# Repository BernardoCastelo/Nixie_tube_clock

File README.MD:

# Cold cathode display clock

## Components:
> - IN12 displays
> - Firebeetle ESP-32
> - NTE74141 BCD−to−Decimal Decoder
> - 74HC4094N 8-bit Shift Register

- https://photos.app.goo.gl/ndDG4vCSE8pfqmn36

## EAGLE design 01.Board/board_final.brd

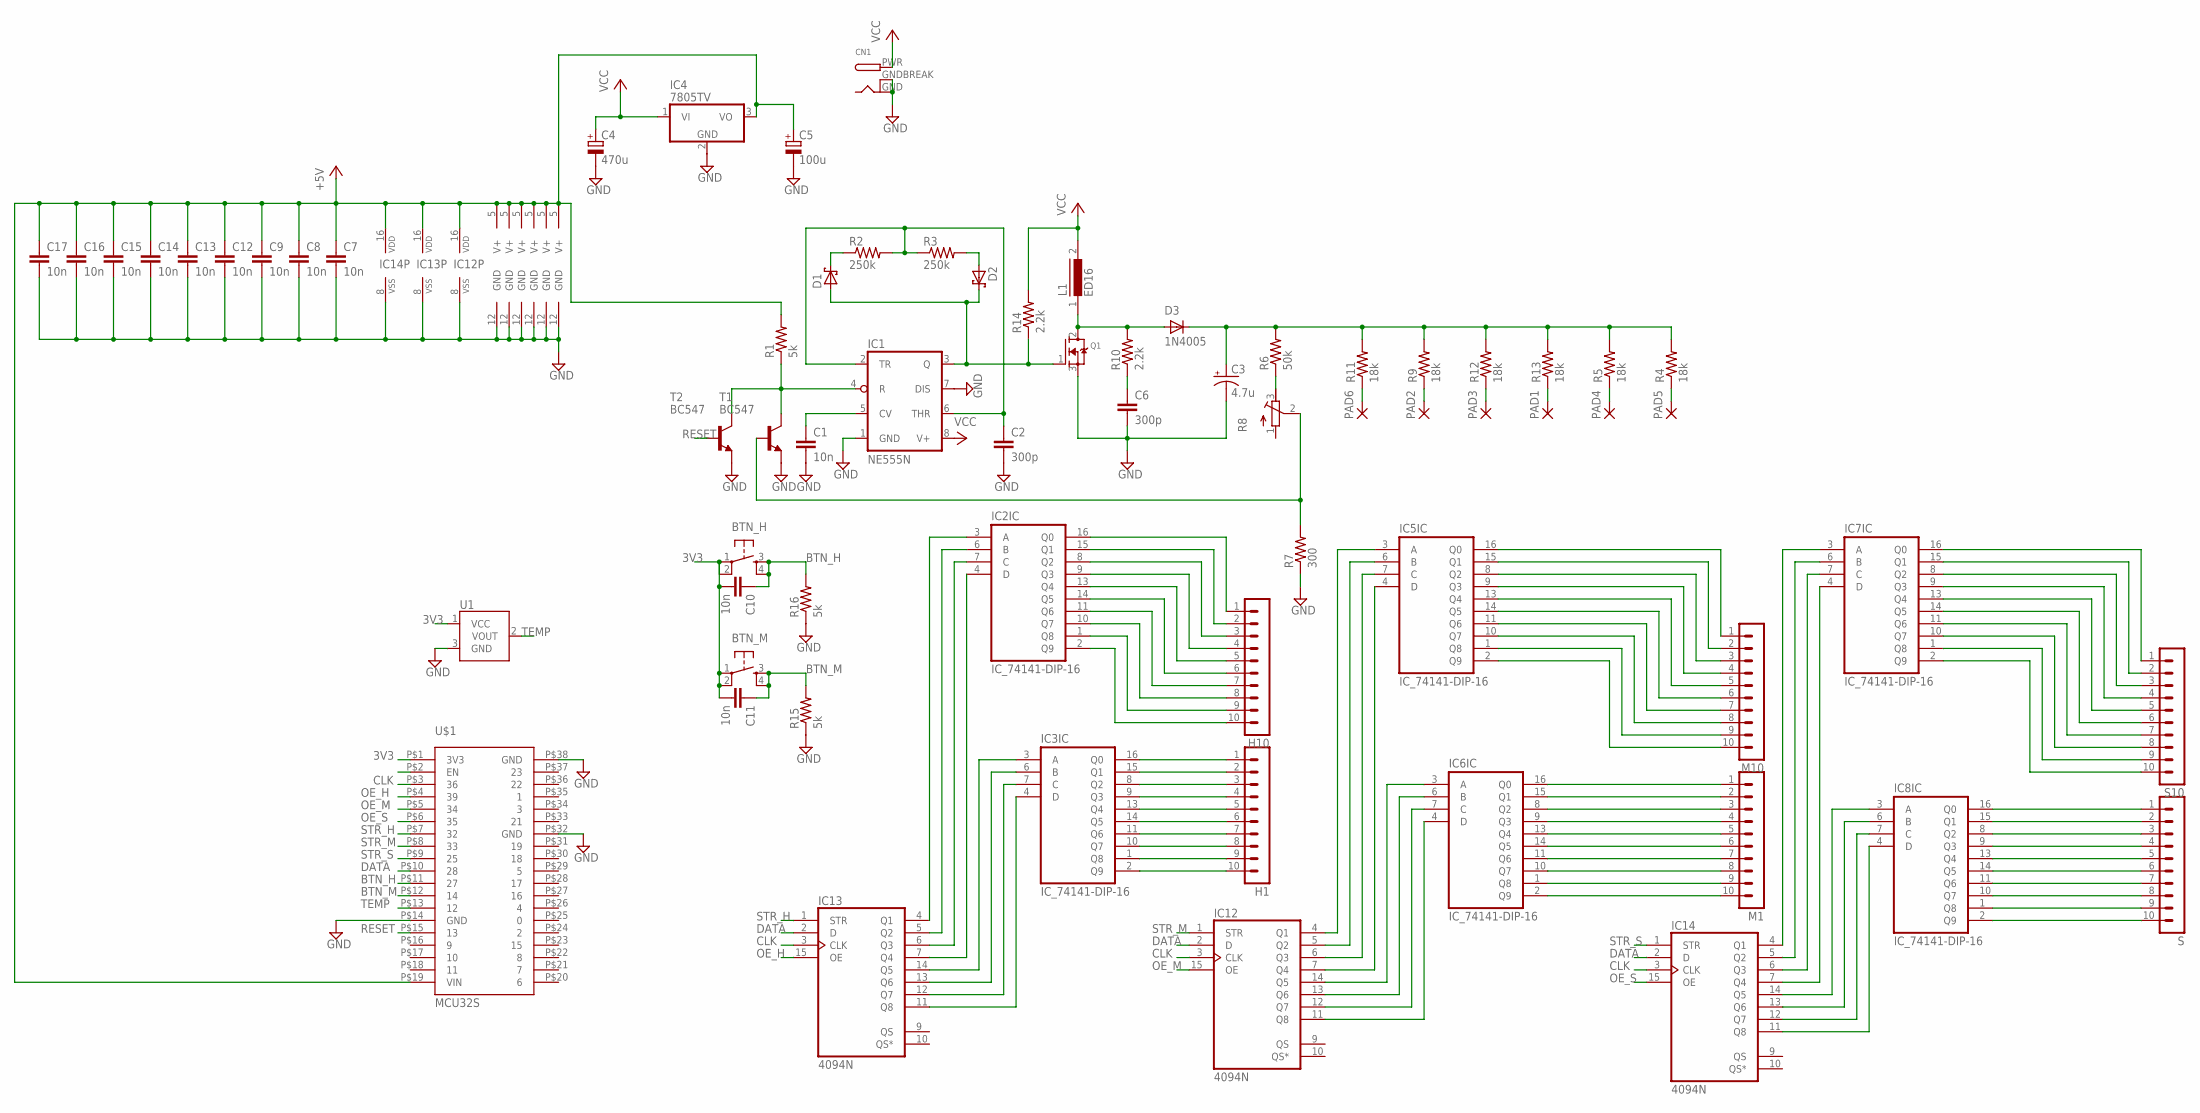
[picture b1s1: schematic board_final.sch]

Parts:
BTN_H: TAC_SWITCHPTH; TACTILE-PTH
BTN_M: TAC_SWITCHPTH; TACTILE-PTH
C1, C7, C8, C9, C10, C11, C12, C13, C14, C15, C16, C17: 10n; C050-030X075
C2, C6: 300p; C050-030X075
C3: 4.7u; E3,5-10
C4: 470u; E5-8,5
C5: 100u; E5-8,5
CN1: DCBARRELPTH; DCJACK_2MM_PTH
D1, D2: SCHOTTKY-DIODEF126Z12; F126Z12
D3: 1N4005; DO41-10
H1, H10: MA10-1
IC1: NE555N; DIL08
IC2, IC3, IC5, IC6, IC7, IC8: IC_74141-DIP-16; DIL16
IC4: 7805TV; TO220V
IC12, IC13, IC14: 4094N; DIL16
L1: ED16
M1, M10: MA10-1
PAD1, PAD2, PAD3, PAD4, PAD5, PAD6: 3,17/1,3
Q1: MOSFET-NGDS_TO220V; TO220V
R1, R15, R16: 5k; 0207/10
R2, R3: 250k; 0207/10
R4, R5, R9, R11, R12, R13: 18k; 0207/10
R6: 50k; 0207/10
R7: 300; 0207/10
R8: R-TRIMM3296W; RTRIM3296W
R10, R14: 2.2k; 0207/10
S, S10: MA10-1
T1, T2: BC547; TO92
U1: TMP36GT9; TO-92
U$1: MCU32S; NODEMCU32S

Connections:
3V3: BTN_H.1, BTN_H.2, BTN_M.1, BTN_M.2, C10.2, C11.2, U1.1 (VCC), U$1.P$1 (3V3)
BTN_H: BTN_H.3, BTN_H.4, C10.1, R16.2, U$1.P$11 (27)
BTN_M: BTN_M.3, BTN_M.4, C11.1, R15.2, U$1.P$12 (14)
CLK: IC12.3 (CLK), IC13.3 (CLK), IC14.3 (CLK), U$1.P$3 (36)
DATA: IC12.2 (D), IC13.2 (D), IC14.2 (D), U$1.P$10 (28)
GND: C1.2, C2.2, C3.-, C4.-, C5.-, C6.2, C7.2, C8.2, C9.2, C12.2, C13.2, C14.2, C15.2, C16.2, C17.2, CN1.GND, CN1.GNDBREAK, IC1.1 (GND), IC1.7 (DIS), IC2.12 (GND), IC3.12 (GND), IC4.2 (GND), IC5.12 (GND), IC6.12 (GND), IC7.12 (GND), IC8.12 (GND), IC12.8 (VSS), IC13.8 (VSS), IC14.8 (VSS), Q1.3 (S), R7.1, R15.1, R16.1, T1.1 (E), T2.1 (E), U1.3 (GND), U$1.P$14 (GND), U$1.P$32 (GND), U$1.P$38 (GND)
unnamed: C1.1, IC1.5 (CV)
unnamed: C2.1, IC1.2 (TR), IC1.6 (THR), R2.2, R3.1
unnamed: C3.+, D3.C, R4.2, R5.2, R6.2, R9.2, R11.2, R12.2, R13.2
unnamed: D1.A, D2.C, IC1.3 (Q), Q1.1 (G), R14.1
unnamed: IC1.4 (R), R1.1, T1.3 (C), T2.3 (C)
unnamed: H10.1, IC2.16 (Q0)
unnamed: D2.A, R3.2
unnamed: D1.C, R2.1
unnamed: IC2.3 (A), IC13.4 (Q1)
unnamed: D3.A, L1.1, Q1.2 (D), R10.2
unnamed: H10.2, IC2.15 (Q1)
unnamed: H10.3, IC2.8 (Q2)
unnamed: H10.4, IC2.9 (Q3)
unnamed: H10.5, IC2.13 (Q4)
unnamed: H10.6, IC2.14 (Q5)
unnamed: H10.7, IC2.11 (Q6)
unnamed: H10.8, IC2.10 (Q7)
unnamed: H10.9, IC2.1 (Q8)
unnamed: H10.10, IC2.2 (Q9)
unnamed: PAD6.1, R11.1
unnamed: IC2.7 (C), IC13.6 (Q3)
unnamed: IC2.6 (B), IC13.5 (Q2)
unnamed: IC2.4 (D), IC13.7 (Q4)
unnamed: H1.1, IC3.16 (Q0)
unnamed: H1.2, IC3.15 (Q1)
unnamed: H1.3, IC3.8 (Q2)
unnamed: C6.1, R10.1
unnamed: H1.4, IC3.9 (Q3)
unnamed: H1.5, IC3.13 (Q4)
unnamed: H1.6, IC3.14 (Q5)
unnamed: H1.7, IC3.11 (Q6)
unnamed: R6.1, R8.3 (E)
unnamed: R7.2, R8.2 (S), T1.2 (B)
unnamed: H1.8, IC3.10 (Q7)
unnamed: H1.9, IC3.1 (Q8)
unnamed: H1.10, IC3.2 (Q9)
unnamed: IC3.7 (C), IC13.12 (Q7)
unnamed: IC3.6 (B), IC13.13 (Q6)
unnamed: IC3.4 (D), IC13.11 (Q8)
unnamed: PAD2.1, R9.1
unnamed: IC3.3 (A), IC13.14 (Q5)
unnamed: IC6.2 (Q9), M1.10
unnamed: IC6.1 (Q8), M1.9
unnamed: IC6.10 (Q7), M1.8
unnamed: IC6.11 (Q6), M1.7
unnamed: IC6.14 (Q5), M1.6
unnamed: IC6.13 (Q4), M1.5
unnamed: IC6.9 (Q3), M1.4
unnamed: IC6.8 (Q2), M1.3
unnamed: IC6.15 (Q1), M1.2
unnamed: IC6.16 (Q0), M1.1
unnamed: IC5.7 (C), IC12.6 (Q3)
unnamed: IC5.6 (B), IC12.5 (Q2)
unnamed: IC5.4 (D), IC12.7 (Q4)
unnamed: PAD3.1, R12.1
unnamed: IC5.3 (A), IC12.4 (Q1)
unnamed: IC5.16 (Q0), M10.1
unnamed: IC5.15 (Q1), M10.2
unnamed: IC5.8 (Q2), M10.3
unnamed: IC5.9 (Q3), M10.4
unnamed: IC5.13 (Q4), M10.5
unnamed: IC5.14 (Q5), M10.6
unnamed: IC5.11 (Q6), M10.7
unnamed: IC5.10 (Q7), M10.8
unnamed: IC5.1 (Q8), M10.9
unnamed: IC5.2 (Q9), M10.10
unnamed: IC6.6 (B), IC12.13 (Q6)
unnamed: IC8.16 (Q0), S.1
unnamed: IC8.15 (Q1), S.2
unnamed: PAD1.1, R13.1
unnamed: IC6.3 (A), IC12.14 (Q5)
unnamed: IC7.3 (A), IC14.4 (Q1)
unnamed: IC8.8 (Q2), S.3
unnamed: IC8.9 (Q3), S.4
unnamed: IC8.13 (Q4), S.5
unnamed: IC8.14 (Q5), S.6
unnamed: IC8.11 (Q6), S.7
unnamed: IC8.10 (Q7), S.8
unnamed: IC8.2 (Q9), S.10
unnamed: IC8.1 (Q8), S.9
unnamed: IC7.16 (Q0), S10.1
unnamed: IC7.6 (B), IC14.5 (Q2)
unnamed: IC7.7 (C), IC14.6 (Q3)
unnamed: IC7.4 (D), IC14.7 (Q4)
unnamed: PAD4.1, R5.1
unnamed: IC8.3 (A), IC14.14 (Q5)
unnamed: IC8.6 (B), IC14.13 (Q6)
unnamed: IC7.15 (Q1), S10.2
unnamed: IC7.8 (Q2), S10.3
unnamed: IC7.9 (Q3), S10.4
unnamed: IC7.13 (Q4), S10.5
unnamed: IC7.14 (Q5), S10.6
unnamed: IC7.11 (Q6), S10.7
unnamed: IC7.10 (Q7), S10.8
unnamed: IC7.1 (Q8), S10.9
unnamed: IC7.2 (Q9), S10.10
unnamed: IC8.7 (C), IC14.12 (Q7)
unnamed: IC8.4 (D), IC14.11 (Q8)
unnamed: PAD5.1, R4.1
unnamed: IC6.7 (C), IC12.12 (Q7)
unnamed: IC6.4 (D), IC12.11 (Q8)
OE_H: IC13.15 (OE), U$1.P$4 (39)
OE_M: IC12.15 (OE), U$1.P$5 (34)
OE_S: IC14.15 (OE), U$1.P$6 (35)
RESET: T2.2 (B), U$1.P$15 (13)
STR_H: IC13.1 (STR), U$1.P$7 (32)
STR_M: IC12.1 (STR), U$1.P$8 (33)
STR_S: IC14.1 (STR), U$1.P$9 (25)
TEMP: U1.2 (VOUT), U$1.P$13 (12)
V+: C5.+, C7.1, C8.1, C9.1, C12.1, C13.1, C14.1, C15.1, C16.1, C17.1, IC2.5 (V+), IC3.5 (V+), IC4.3 (VO), IC5.5 (V+), IC6.5 (V+), IC7.5 (V+), IC8.5 (V+), IC12.16 (VDD), IC13.16 (VDD), IC14.16 (VDD), R1.2, U$1.P$19 (VIN)
VCC: C4.+, CN1.PWR, IC1.8 (V+), IC4.1 (VI), L1.2, R14.2

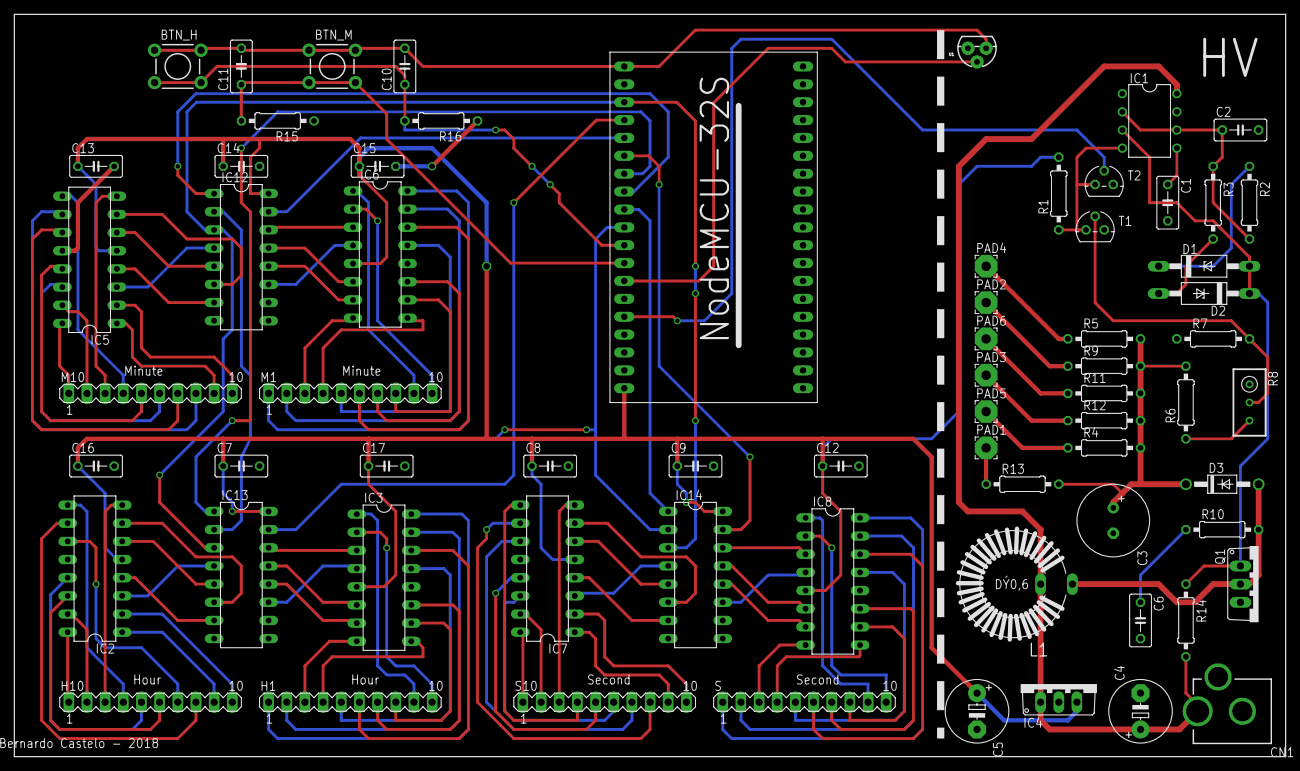
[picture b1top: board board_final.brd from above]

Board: 2 copper layers, 177.8 x 103.8 mm, 68 parts (0 on the bottom side), 117 nets.

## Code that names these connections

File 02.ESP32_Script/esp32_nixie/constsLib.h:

#define CLK_PIN 22
#define CLK 0
#define OE_H 39
#define OE_M 34
#define OE_S 35
#define STR_H 32
#define STR_M 33
#define STR_S 25
#define DATA_PIN 26
#define BTN_H 27
#define BTN_M 14
#define TEMP_PIN 12
#define RESET 13
#define OFF_CODE 0b1111

const char *ssid = "";
const char *password = "";
const char *ntpServer = "pool.ntp.org";
const long gmtOffset_sec = 0;
int daylightOffset_sec = 0;
const int ntpGetPeriod = 18000000;
enum DigitType
{
  SECOND,
  MINUTE,
  HOUR
};

void writeDisplay(DigitType type, byte value);

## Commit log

2021-02-21 init
2021-03-27 Added DST offset.
2021-03-28 Fixed DST hour update

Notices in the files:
parts and their libraries:
SparkFun: Licensing: CC v3.0 Share-Alike You are welcome to use this library for commercial purposes.
